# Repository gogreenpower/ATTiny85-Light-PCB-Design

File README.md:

# ATTiny85-Light-PCB-Design
First attempt at designing a PCB

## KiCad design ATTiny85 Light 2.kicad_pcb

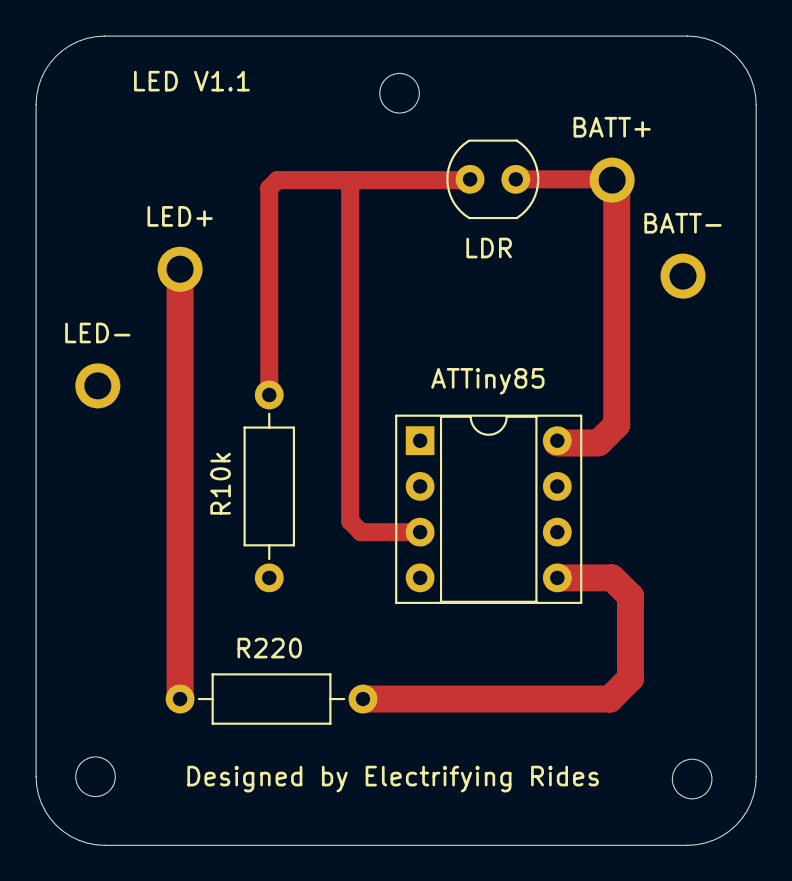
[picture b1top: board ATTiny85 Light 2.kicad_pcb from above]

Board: 2 copper layers, 40.0 x 45.0 mm, 11 parts (0 on the bottom side), 5 nets.

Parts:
ATTiny85: ATtiny85-20PU; DIP-8_W7.62mm_Socket
BATT+: MountingHole_Pad; MountingHole_2.2mm_M2_DIN965_Pad
BATT-: MountingHole_Pad; MountingHole_2.2mm_M2_DIN965_Pad
H1, H4, H6: MountingHole; MountingHole_2.2mm_M2
LDR: LDR; R_LDR_4.9x4.2mm_P2.54mm_Vertical
LED+: MountingHole_Pad; MountingHole_2.2mm_M2_DIN965_Pad
LED-: MountingHole_Pad; MountingHole_2.2mm_M2_DIN965_Pad
R10k: R 220; R_Axial_DIN0207_L6.3mm_D2.5mm_P10.16mm_Horizontal
R220: R 10k; R_Axial_DIN0207_L6.3mm_D2.5mm_P10.16mm_Horizontal

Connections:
GND: ATTiny85.4, BATT-.1, LED-.4, R10k.2
unnamed: LED+.3, R220.1
unnamed: ATTiny85.5, R220.2
unnamed: ATTiny85.3, LDR.1, R10k.1
VCC: ATTiny85.8, BATT+.2, LDR.2
